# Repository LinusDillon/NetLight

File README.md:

# NetLight
ESP8266 driven NeoPixel Controller

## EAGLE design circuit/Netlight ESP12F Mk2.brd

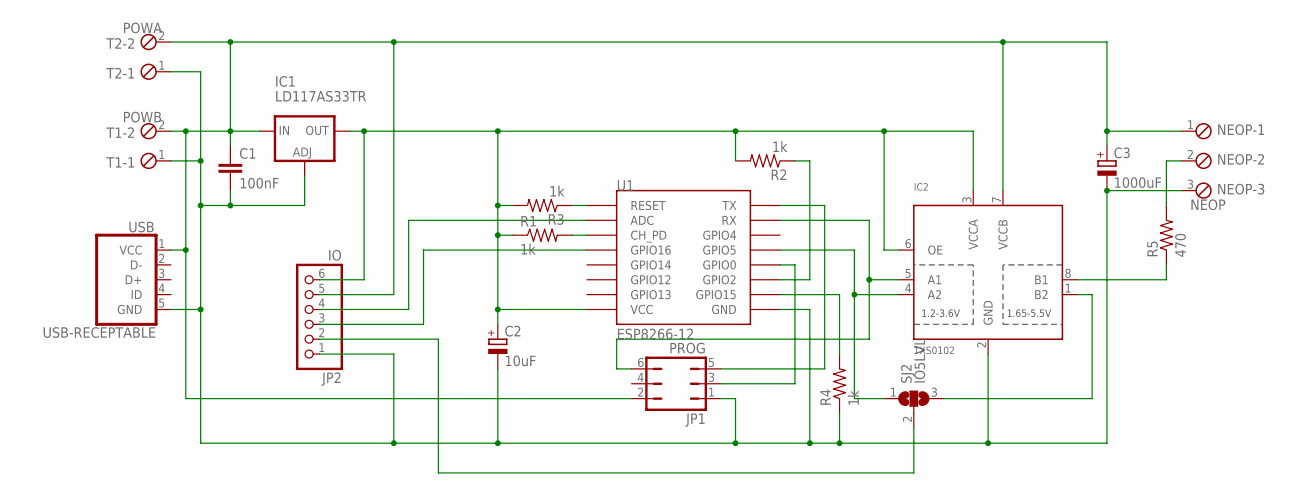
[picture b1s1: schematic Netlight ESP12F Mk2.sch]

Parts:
C1: 100nF; C1206
C2: 10uF; CT3528
C3: 1000uF; PANASONIC_G
IC1: LD117AS33TR; SOT223
IC2: TXS0102; TI-SM8
JP1: PROG; JP3Q
JP2: IO; 1X06
NEOP: NEOP; 3POL254
R1, R2, R3, R4: 1k; R0805
R5: 470; R0805
SJ2: IO5LVL; SJ_2
T1: POWB; 2POL254
T2: POWA; 2POL254
U1: ESP8266-12; ESP12-SMD
USB: USB-RECEPTABLE; FCI-10103594-0001LF

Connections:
+3.3V: C2.+, IC1.4 (OUT), IC2.3 (VCCA), IC2.6 (OE), JP2.6, R1.1, R2.2, R3.2, U1.VCC
+5V: C1.1, C3.+, IC1.3 (IN), IC2.7 (VCCB), JP1.2, JP2.5, NEOP.1, T1.2, T2.2, USB.1 (VCC)
GND: C1.2, C2.-, C3.-, IC1.1 (ADJ), IC2.2 (GND), JP1.1, JP2.1, NEOP.3, R4.1, T1.1, T2.1, U1.GND, USB.5 (GND)
unnamed: R2.1, U1.GPIO2
unnamed: JP2.4, U1.ADC
unnamed: JP2.3, U1.GPIO16
unnamed: R1.2, U1.CH_PD
unnamed: R3.1, U1.RESET
unnamed: R4.2, U1.GPIO15
unnamed: IC2.5 (A1), JP1.6, U1.RXD0 (RX)
unnamed: IC2.8 (B1), R5.1
unnamed: NEOP.2, R5.2
unnamed: IC2.4 (A2), SJ2.1, U1.GPIO5
unnamed: JP1.3, U1.GPIO0
unnamed: JP1.5, U1.TXD0 (TX)
unnamed: JP2.2, SJ2.2
unnamed: IC2.1 (B2), SJ2.3

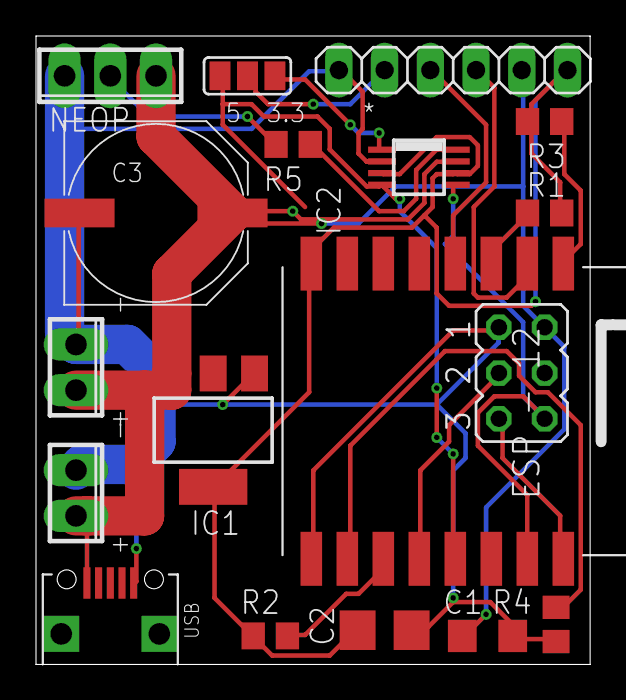
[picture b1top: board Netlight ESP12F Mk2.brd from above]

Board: 2 copper layers, 30.8 x 34.9 mm, 18 parts (0 on the bottom side), 17 nets.

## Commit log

2016-08-03 Initial checkin
2016-08-22 Added EagleCAD schematic/board
